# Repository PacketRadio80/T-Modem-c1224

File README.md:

# T-Modem-c1224

**Prototype Notice:** This repository contains hardware prototypes that have **passed all automated software tests** (unit, integration, stress). **Practical field testing with real radio equipment is still pending.** Use at your own risk. GPLv3 — non-profit.

---

USB KISS half-TNC for Raspberry Pi Pico. Chip PHY via TCM3105-class modem IC with crystal-selected baud rate (1200 / 2400). HDLC + bitbang TX/RXD, PTT, LCD display, sense inputs.

**Firmware language:** C · **License:** GPLv3 · **Platform:** RP2040 (Raspberry Pi Pico)

**Docs:** [`docs/dok/README.md`](docs/dok/README.md) — complete documentation (build · flash · commission · operate · host · troubleshooting).

## Firmware Images

Pre-built UF2 files in `firmware/c1224/bin/`:

| File | Baud | Crystal | Description |
|------|------|---------|-------------|
| `c1224-1200.uf2` | 1200 | Y1 (4.4336 MHz) | Bell-202 AFSK standard |
| `c1224-2400.uf2` | 2400 | Y2 (6.5536 MHz) | Higher-rate packet |

**One board = one rate = one crystal.** Rebuild firmware if you change crystals.

## Quick Guide — Firmware Update

### Prerequisites
- Raspberry Pi Pico with USB cable
- T-Modem-c1224 board (or any RP2040 board for testing)

### Flash via BOOTSEL (Recommended)

1. **Disconnect** the Pico from USB.
2. **Hold the BOOTSEL button** on the Pico while plugging in USB.
3. The Pico appears as a USB mass storage device (`RPI-RP2`).
4. **Copy** the appropriate `.uf2` file to the `RPI-RP2` drive:
   ```bash
   # Linux
   cp firmware/c1224/bin/c1224-2400.uf2 /media/$USER/RPI-RP2/
   ```
5. The Pico **automatically reboots** and runs the new firmware.
6. Verify: open `/dev/ttyACM0` at 115200 baud, send `STATUS` → should respond.

### Flash via picotool (Advanced)

```bash
picotool load firmware/c1224/bin/c1224-2400.uf2 -x
```

**Unattended (CLI):** send `BOOTSEL` (or `DFU`) to enter the UF2 bootloader, `REBOOT` to restart. Opening the port at **1200 baud** and dropping **DTR** also enters the bootloader (classic 1200bps touch).

### Build from Source

```bash
export PICO_SDK_PATH=/path/to/pico-sdk
cd firmware/c1224
mkdir build && cd build
cmake .. -DC1224_BITRATE=2400   # 1200 or 2400
make -j$(nproc)
# → c1224.uf2
```

## Operation

1. Power from **12 V** barrel (centre-positive). USB = data only.
2. Connect USB to host. Open `/dev/ttyACM0` at 115200 baud.
3. **KISS mode:** Send `0xC0`-framed packets (standard KISS TNC).
4. **Service mode:** Send ASCII commands (`HELP`, `STATUS`, `PTT ON/OFF`, `ID`).

### ASCII Commands

| Command | Description |
|---------|-------------|
| `HELP` | List available commands |
| `STATUS` | Show modem state, PTT, signal, bitrate |
| `ID` | Show device ID, callsign, bitrate |
| `PTT ON` / `PTT OFF` | Manual PTT control |
| `QUIET ON/OFF` | Enable/disable unsolicited output |
| `INI` | Dump configuration |
| `GET <key>` | Read config value |
| `SET <key>=<value>` | Set config value (RAM only) |
| `SAVE` | Persist config to flash |
| `RELOAD` | Reload config from flash |
| `DEFAULTS` | Reset to factory defaults |
| `BOOTSEL` / `DFU` | Enter UF2 bootloader (unattended flash) |
| `REBOOT` | Restart the firmware |

## Hardware

- **Schematic:** `hardware/kicad/`
- **BOM:** `hardware/BOM.md` and `hardware/bom/BOM.csv`
- **Crystal:** Y1 (4.4336 MHz) for 1200 baud, Y2 (6.5536 MHz) for 2400 baud
- **PTT:** GP9 → optocoupler → radio PTT input
- **Sense:** GP8 (CDT/carrier detect), GP7 (RXD/packet detect)
- **Display:** I2C HD44780 via PCF8574 backpack (optional)
- **Missing component (nachrüstbar):** the PCB has **no TX AF output buffer** → weak/distorted TX audio (TCM3105 `TXA` needs ≥50 kΩ load, but `RV1` loads it with 10 kΩ). **Retrofit (Lösung 1):** unity-gain op-amp buffer between `TXA` and `RV1` — see `hardware/BOM.md` §6.1.

## Architecture

```
Host (USB CDC) ←→ Pico (RP2040) ←→ TCM3105 modem chip ←→ Radio
                  │
                  ├── KISS parser (0xC0 framing)
                  ├── HDLC encode/decode
                  ├── AFSK bitbang (GP6 TXD, GP7 RXD)
                  ├── PTT control (GP9)
                  ├── Sense (GP8 CDT, GP7 RXD)
                  ├── I2C display (optional)
                  └── Config (flash storage)
```

## Project Structure

```
T-Modem-c1224/
├── firmware/c1224/
│   ├── src/common/          # C source files
│   ├── include/             # Headers
│   ├── config/              # Default INI
│   ├── bin/                 # Pre-built UF2 images
│   └── CMakeLists.txt
├── hardware/
│   ├── kicad/               # Schematic + PCB
│   ├── bom/                 # Bill of materials
│   └── BOM.md
├── docs/                    # User guide, figures
└── share/                   # Example INI files
```

## License

GNU General Public License v3.0 — see [LICENSE](LICENSE).

**Non-profit project.** Not for commercial use without permission.

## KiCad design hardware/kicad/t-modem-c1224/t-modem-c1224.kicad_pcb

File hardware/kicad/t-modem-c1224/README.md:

# KiCad — T-Modem-c1224

| File | Role |
|------|------|
| `t-modem-c1224.kicad_sch` | Schematic |
| `t-modem-c1224.kicad_pcb` | PCB **180×180 mm** · fab-ready (DRC clean) |
| `t-modem-c1224.kicad_pro` | Project |
| `t-modem-c1224.kicad_sym` | Symbols |
| `sym-lib-table` | Symbol library table |
| `t-modem-c1224.rules` | Custom DRC rules |
| `scripts/` | Layer/docs helpers |

Tag: **v1.0-prototype**. AS-IS · GPLv3 non-profit.

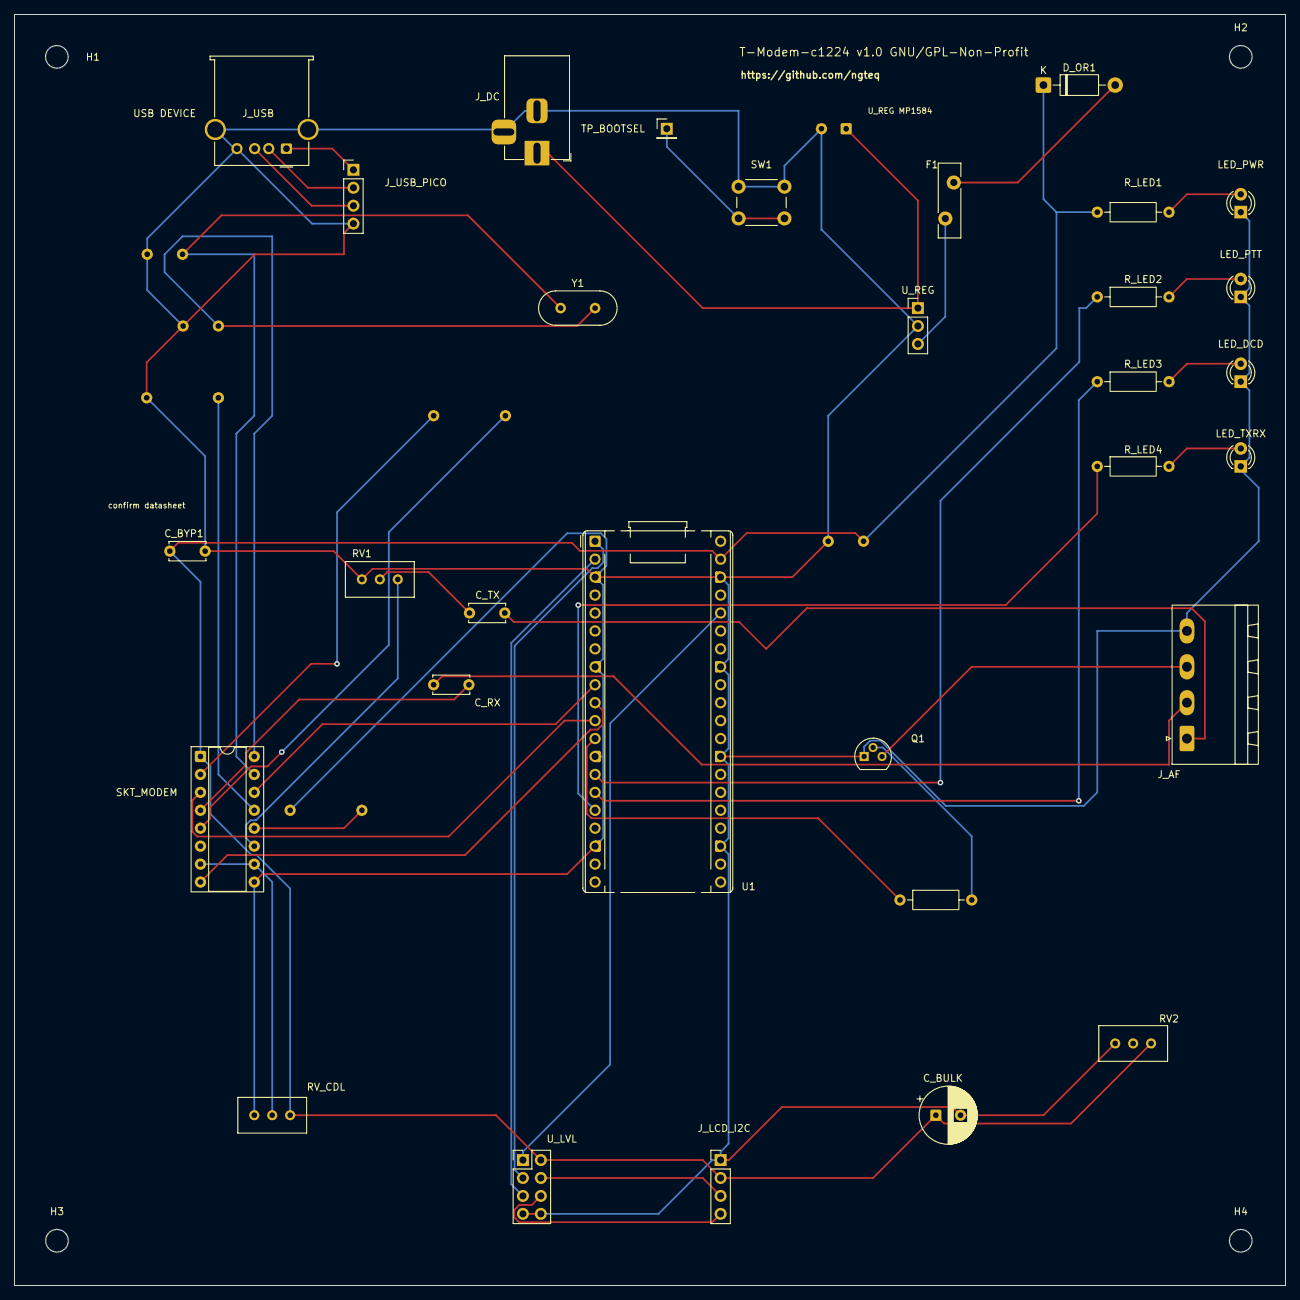
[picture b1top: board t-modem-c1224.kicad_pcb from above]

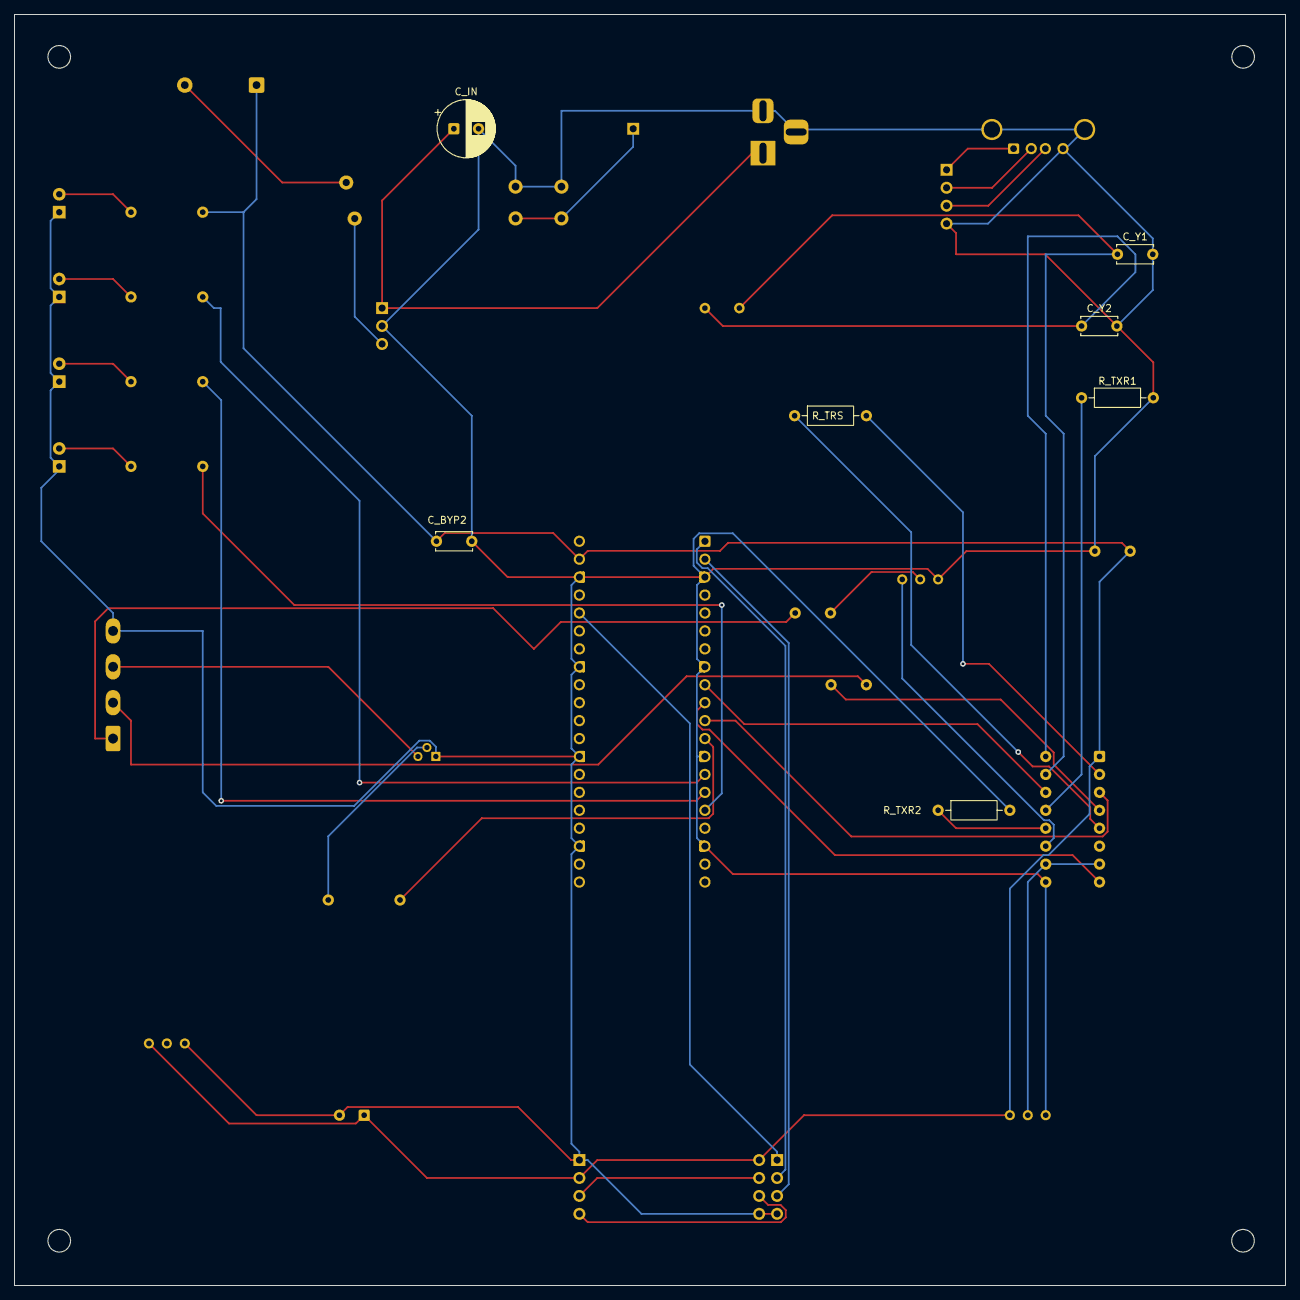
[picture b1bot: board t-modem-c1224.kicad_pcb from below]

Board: 2 copper layers, 180.0 x 180.0 mm, 42 parts (7 on the bottom side), 39 nets.

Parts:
C_BULK: 100uF; CP_Radial_D8.0mm_P3.50mm
C_BYP1, C_BYP2: 100nF; C_Disc_D5.0mm_W2.5mm_P5.00mm
C_IN: 100uF; CP_Radial_D8.0mm_P3.50mm
C_RX: 100nF; C_Disc_D5.0mm_W2.5mm_P5.00mm
C_TX: 100nF; C_Disc_D5.0mm_W2.5mm_P5.00mm
C_Y1, C_Y2: 22pF; C_Disc_D5.0mm_W2.5mm_P5.00mm
D_OR1: 1N5819; D_DO-41_SOD81_P10.16mm_Horizontal
F1: MF-RG500; Fuse_Bourns_MF-RG500
H1, H2, H3, H4: M3; MountingHole_3.2mm_M3
J_AF: AF; PhoenixContact_MSTBA_2,5_4-G-5,08_1x04_P5.08mm_Horizontal
J_DC: 12V CENTRE; BarrelJack_Horizontal
J_LCD_I2C: LCD I2C; PinHeader_1x04_P2.54mm_Vertical
J_USB: USB_A; USB_A_Molex_67643_Horizontal
J_USB_PICO: Pico Micro-USB cable; PinHeader_1x04_P2.54mm_Vertical
LED_DCD: DCD; LED_D3.0mm
LED_PTT: PTT; LED_D3.0mm
LED_PWR: PWR; LED_D3.0mm
LED_TXRX: TXRX; LED_D3.0mm
Q1: 2N2222A; TO-92
RV1: 10k TX; Potentiometer_Bourns_3296W_Vertical
RV2: 10k contrast; Potentiometer_Bourns_3296W_Vertical
RV_CDL: 50k CDL; Potentiometer_Bourns_3296W_Vertical
R_LED1, R_LED2, R_LED3, R_LED4: 1k; R_Axial_DIN0207_L6.3mm_D2.5mm_P10.16mm_Horizontal
R_PTT: 4.7k; R_Axial_DIN0207_L6.3mm_D2.5mm_P10.16mm_Horizontal
R_TRS: 0R; R_Axial_DIN0207_L6.3mm_D2.5mm_P10.16mm_Horizontal
R_TXR1, R_TXR2: 0R; R_Axial_DIN0207_L6.3mm_D2.5mm_P10.16mm_Horizontal
SKT_MODEM: U_MODEM TCM3105; DIP-16_W7.62mm_Socket
SW1: BOOTSEL; SW_PUSH_6mm
TP_BOOTSEL: Pico BOOTSEL; PinHeader_1x01_P2.54mm_Vertical
U1: RPi-Pico; RaspberryPi_Pico_Common_THT
U_LVL: BSS138; PinHeader_2x04_P2.54mm_Vertical
U_REG: Mini560-5V; PinHeader_1x03_P2.54mm_Vertical
Y1: 4.4336/6.5536Mhz; Crystal_HC49-U_Vertical

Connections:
3V3: U1.36, U_LVL.1
+5V: D_OR1.2, F1.2
+5V_OR: C_BULK.1, C_BYP1.1, C_BYP2.1, D_OR1.1, J_LCD_I2C.2, RV2.1, RV_CDL.1, R_LED1.1, SKT_MODEM.1, U1.39, U_LVL.2
+5V_REG: F1.1, U_REG.3
AF_RX: C_RX.1, J_AF.2
AF_TX: C_TX.2, J_AF.1
BOOTSEL: SW1.2, TP_BOOTSEL.1
CDL: RV_CDL.2, SKT_MODEM.7, SKT_MODEM.10
GND: C_BULK.2, C_BYP1.2, C_BYP2.2, C_IN.2, C_Y1.2, C_Y2.2, J_AF.4, J_DC.2, J_DC.3, J_LCD_I2C.1, J_USB.4, J_USB.SH, J_USB_PICO.4, LED_DCD.1, LED_PTT.1, LED_PWR.1, LED_TXRX.1, Q1.1, RV1.3, RV2.3, RV_CDL.3, R_TXR1.2, R_TXR2.2, SKT_MODEM.9, SW1.1, U1.3, U1.8, U1.13, U1.18, U1.23, U1.28, U1.33, U1.38, U_LVL.7, U_LVL.8, U_REG.2
I2C_SCL_3V3: U1.2, U_LVL.5
I2C_SCL_5V: J_LCD_I2C.4, U_LVL.6
I2C_SDA_3V3: U1.1, U_LVL.3
I2C_SDA_5V: J_LCD_I2C.3, U_LVL.4
LED_DCD_A: LED_DCD.2, R_LED3.2
LED_DCD_N: R_LED3.1, U1.15
LED_PTT_A: LED_PTT.2, R_LED2.2
LED_PTT_N: R_LED2.1, U1.14
LED_PWR_A: LED_PWR.2, R_LED1.2
LED_TXRX_A: LED_TXRX.2, R_LED4.2
LED_TXRX_N: R_LED4.1, U1.16
MODEM_CDT: SKT_MODEM.3, U1.11
MODEM_CLK: R_TRS.2, SKT_MODEM.2
MODEM_RXD: SKT_MODEM.8, U1.10
MODEM_TXD: SKT_MODEM.14, U1.9
OSC1: C_Y1.1, SKT_MODEM.15, Y1.1
OSC2: C_Y2.1, SKT_MODEM.16, Y1.2
PTT_B: Q1.2, R_PTT.2
PTT_DRV: R_PTT.1, U1.12
PTT_OC: J_AF.3, Q1.3
RXA: C_RX.2, SKT_MODEM.4
TRS_N: R_TRS.1, SKT_MODEM.5
TXA: RV1.1, SKT_MODEM.11
TXR1_N: R_TXR1.1, SKT_MODEM.13
TXR2_N: R_TXR2.1, SKT_MODEM.12
TX_LVL: C_TX.1, RV1.2
USB_DM: J_USB.2, J_USB_PICO.2
USB_DP: J_USB.3, J_USB_PICO.3
USB_VBUS_NC: J_USB.1, J_USB_PICO.1
VIN_12: C_IN.1, J_DC.1, U_REG.1

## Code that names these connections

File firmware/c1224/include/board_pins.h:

/**
 * T-Modem-c1224 pin map (service Pico — not softmodem).
 * Frozen copper intent (v0.25 schematic) reused as planning default for 180×180.
 * GP14/GP15 = unused mux placeholders for v1.0 (single-XTAL; stuff matches image).
 */
#ifndef C1224_BOARD_PINS_H
#define C1224_BOARD_PINS_H

#include <stdint.h>
#include <stdbool.h>

/* I2C LCD (shared-kit class; level-shifted on board) */
#define PIN_I2C_SDA           0  /* GP0 */
#define PIN_I2C_SCL           1  /* GP1 */
#define I2C_LCD_BAUDRATE      100000
#define I2C_LCD_ADDR_DEFAULT  0x27  /* common PCF8574 backpack; probe may fail → log-only */

/* Modem chip digital (TCM3105-class) — Pico does NOT generate AFSK */
#define PIN_MODEM_TXD         6  /* GP6 → chip TXD */
#define PIN_MODEM_RXD         7  /* GP7 ← chip RXD → Packet UI sense (required · status only) */
#define PIN_MODEM_CDT         8  /* GP8 ← chip CDT → Signal/RX (required) */

/* PTT keying: Pico GPIO → OC → radio PTT (USB CDC service). Not the TX LED. */
#define PIN_PTT_DRV           9  /* GP9 · required for USB PTT ON */

/*
 * Status LEDs (c1224 copper — active-high source via series R; LED cathode = GND).
 * LED_PWR is NOT a GPIO: +5V_OR → R_LED1 → LED_PWR → GND (rail Power indicator).
 *
 * Settled UI (2026-07-26):
 *   - Dual sense REQUIRED: CDT→GP8 Signal/RX · RXD→GP7 Packet (status only, not data bridge).
 *   - CDT = carrier/tone · RXD activity ≠ full AX.25 decode.
 *   - LED_PTT (GP10) = OPTIONAL/SPARE — not required product TX indicator.
 *   - Display TX optional; PTT keying GPIO (GP9) stays separate from LED_PTT.
 *   - LED_TXRX = spare/activity.
 */
#define PIN_LED_PTT           10 /* GP10 · LED_PTT_N · optional/spare (not required TX LED) */
#define PIN_LED_DCD           11 /* GP11 · LED_DCD_N · optional RX mirror of CDT */
#define PIN_LED_TXRX          12 /* GP12 · LED_TXRX_N · spare / optional activity */

/*
 * Crystal mux placeholders — UNUSED for v1.0.
 * Product: one crystal stuffed matching flash (Y1 4.4336 / Y2 6.5536).
 * Dual/mux path abandoned; crystal_steer is a no-op.
 * Optional keep defines if mux ever returns later.
 */
#define PIN_XTAL_SEL_A        14 /* GP14 — unused v1.0 */
#define PIN_XTAL_SEL_B        15 /* GP15 — unused v1.0 */

void board_pins_init(void);

#endif /* C1224_BOARD_PINS_H */

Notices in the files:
hardware/kicad/t-modem-c1224/t-modem-c1224.kicad_pcb:
GNU/GPLv3-Non-Profit (as-is)
T-Modem-c1224 v1.0 GNU/GPL-Non-Profit
